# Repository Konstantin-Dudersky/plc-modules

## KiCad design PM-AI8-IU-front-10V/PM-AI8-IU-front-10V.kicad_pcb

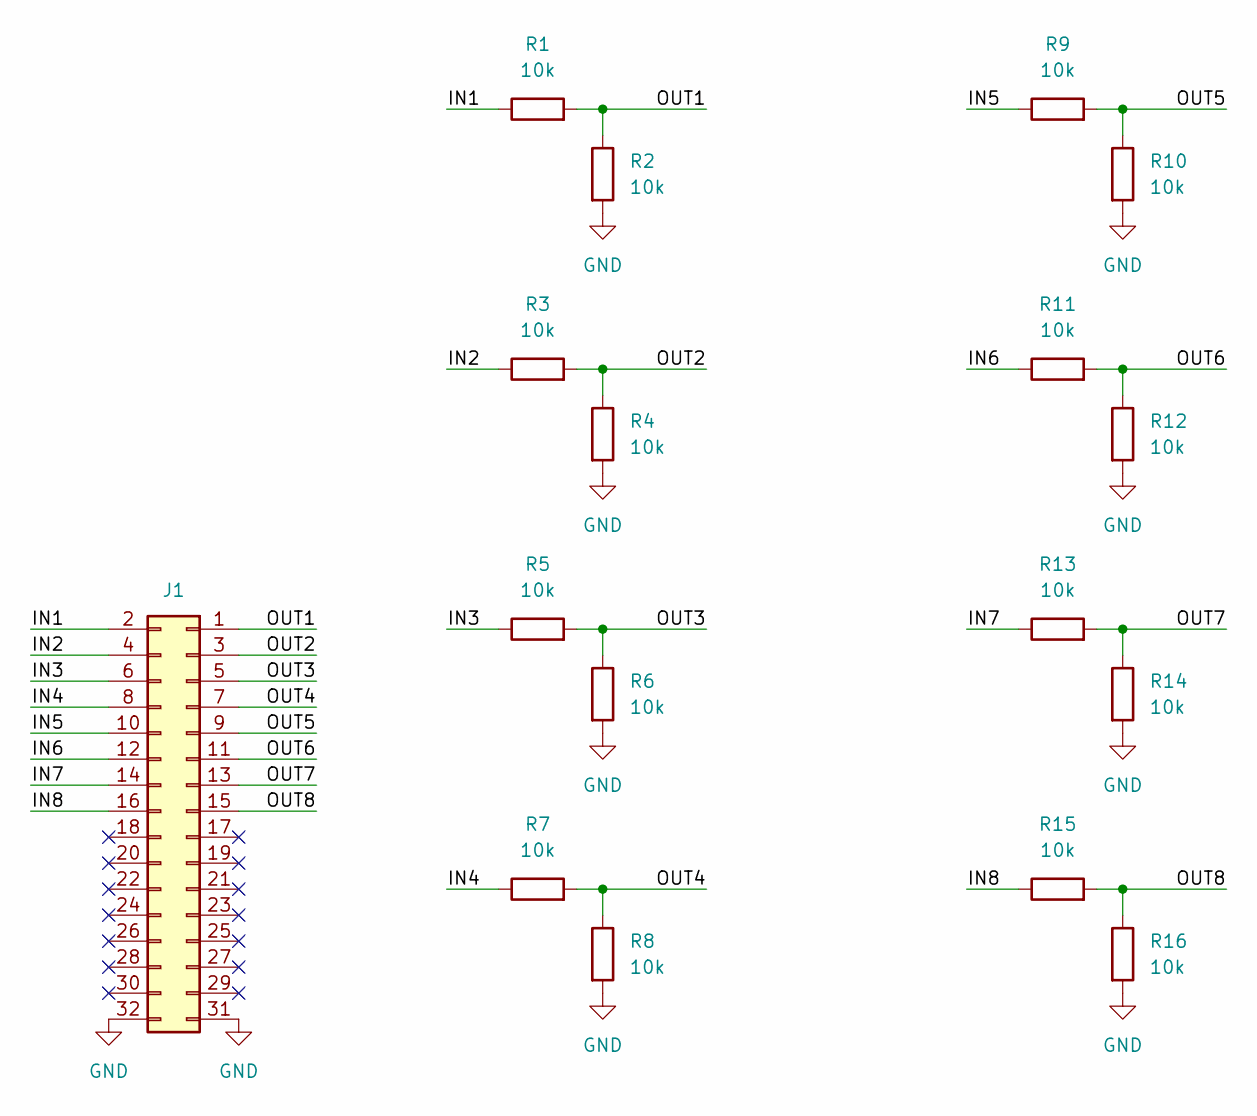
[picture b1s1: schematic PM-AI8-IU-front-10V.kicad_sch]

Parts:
J1: PinHeader P2.54 02x16 SMD Straight; PinHeader_2x16_P2.54mm_Vertical_SMD; part_ipn PinHeader P2.54 02x16 SMD Straight
R1, R2, R3, R4, R5, R6, R7, R8, R9, R10, R11, R12, R13, R14, R15, R16: 10k; R_1206_3216Metric_Pad1.30x1.75mm_HandSolder; part_ipn R_10k_1206_1%

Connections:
/IN1: J1.2, R1.1
/IN2: J1.4, R3.1
/IN3: J1.6, R5.1
/IN4: J1.8, R7.1
/IN5: J1.10, R9.1
/IN6: J1.12, R11.1
/IN7: J1.14, R13.1
/IN8: J1.16, R15.1
/OUT1: J1.1, R1.2, R2.1
/OUT2: J1.3, R3.2, R4.1
/OUT3: J1.5, R5.2, R6.1
/OUT4: J1.7, R7.2, R8.1
/OUT5: J1.9, R9.2, R10.1
/OUT6: J1.11, R11.2, R12.1
/OUT7: J1.13, R13.2, R14.1
/OUT8: J1.15, R15.2, R16.1
GND: J1.31, J1.32, R2.2, R4.2, R6.2, R8.2, R10.2, R12.2, R14.2, R16.2

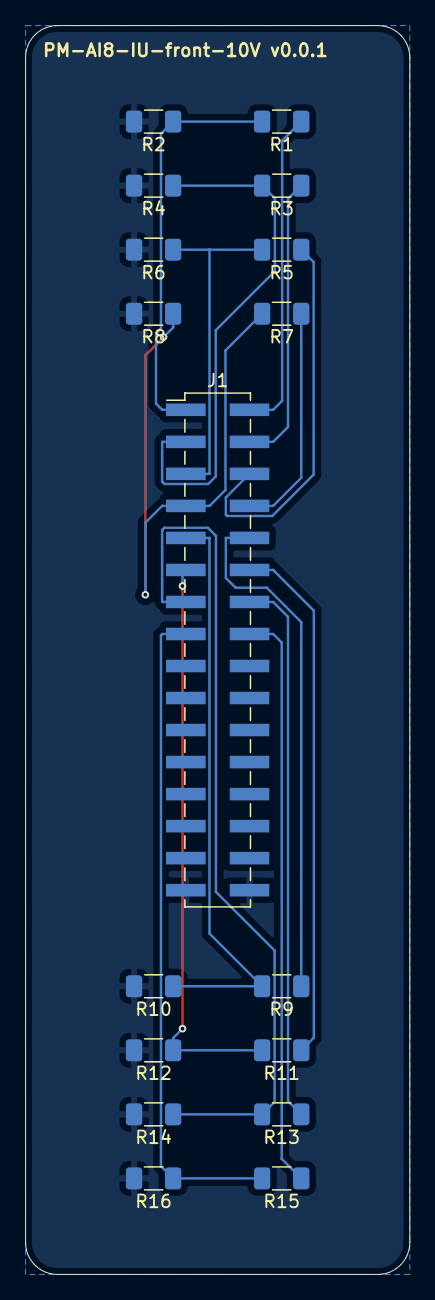
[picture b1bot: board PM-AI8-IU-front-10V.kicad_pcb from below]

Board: 2 copper layers, 30.5 x 99.1 mm, 17 parts (17 on the bottom side), 17 nets.

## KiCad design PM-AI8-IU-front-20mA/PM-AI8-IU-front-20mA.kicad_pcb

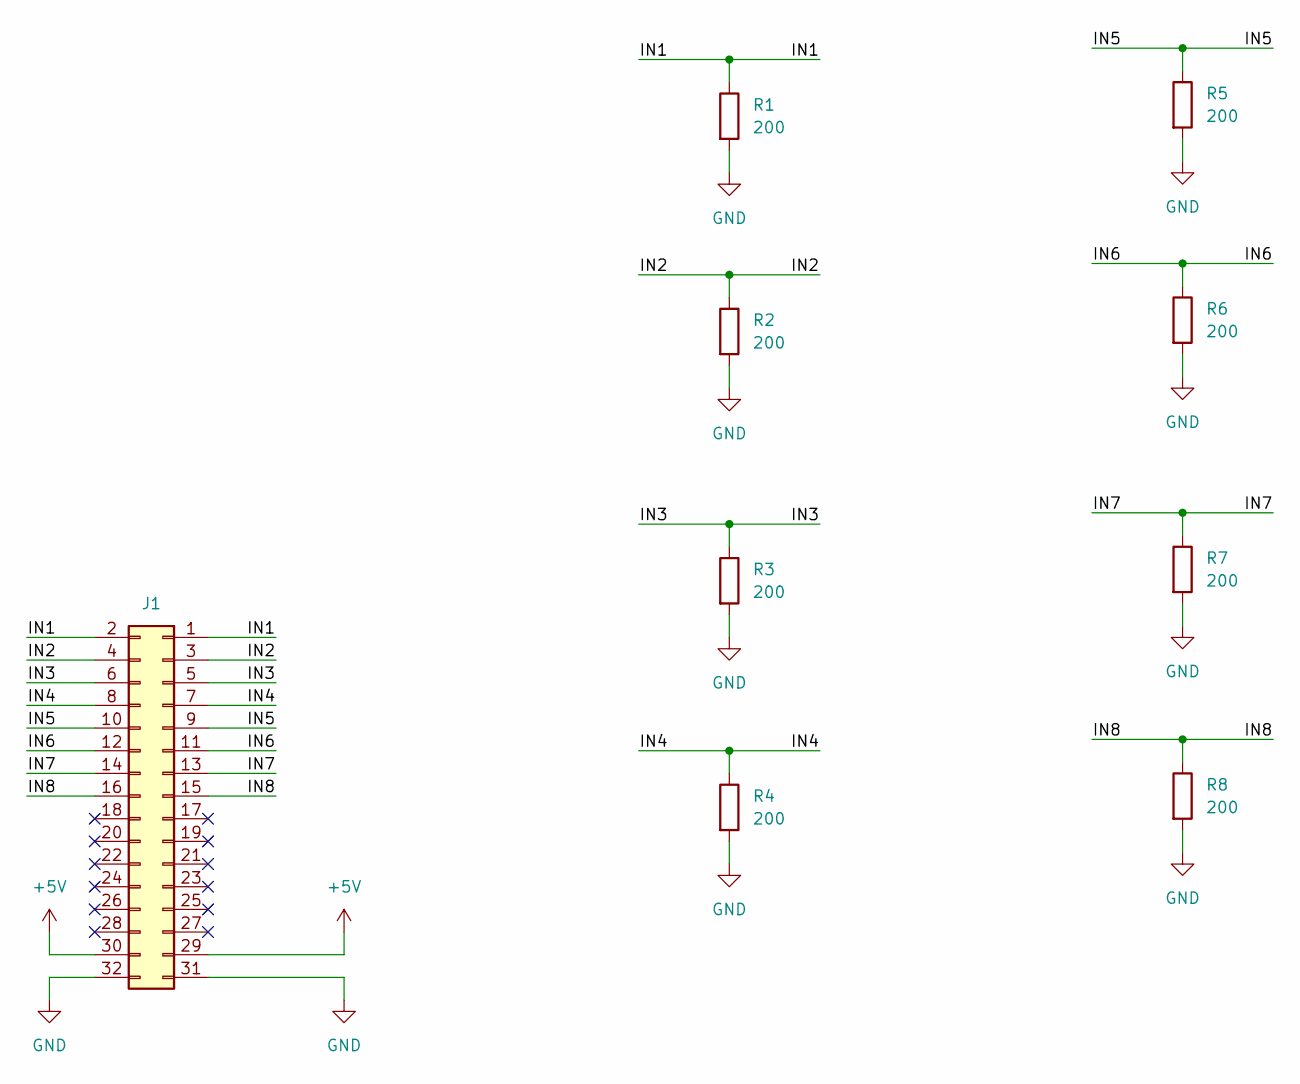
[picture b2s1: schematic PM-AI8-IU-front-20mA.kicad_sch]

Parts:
J1: PinHeader P2.54 02x16 SMD Straight; PinHeader_2x16_P2.54mm_Vertical_SMD; part_ipn PinHeader P2.54 02x16 SMD Straight
R1, R2, R3, R4, R5, R6, R7, R8: 200; R_1206_3216Metric_Pad1.30x1.75mm_HandSolder; part_ipn R_200_1206_0.1%

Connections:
+5V: J1.29, J1.30
/IN1: J1.1, J1.2, R1.1
/IN2: J1.3, J1.4, R2.1
/IN3: J1.5, J1.6, R3.1
/IN4: J1.7, J1.8, R4.1
/IN5: J1.9, J1.10, R5.1
/IN6: J1.11, J1.12, R6.1
/IN7: J1.13, J1.14, R7.1
/IN8: J1.15, J1.16, R8.1
GND: J1.31, J1.32, R1.2, R2.2, R3.2, R4.2, R5.2, R6.2, R7.2, R8.2

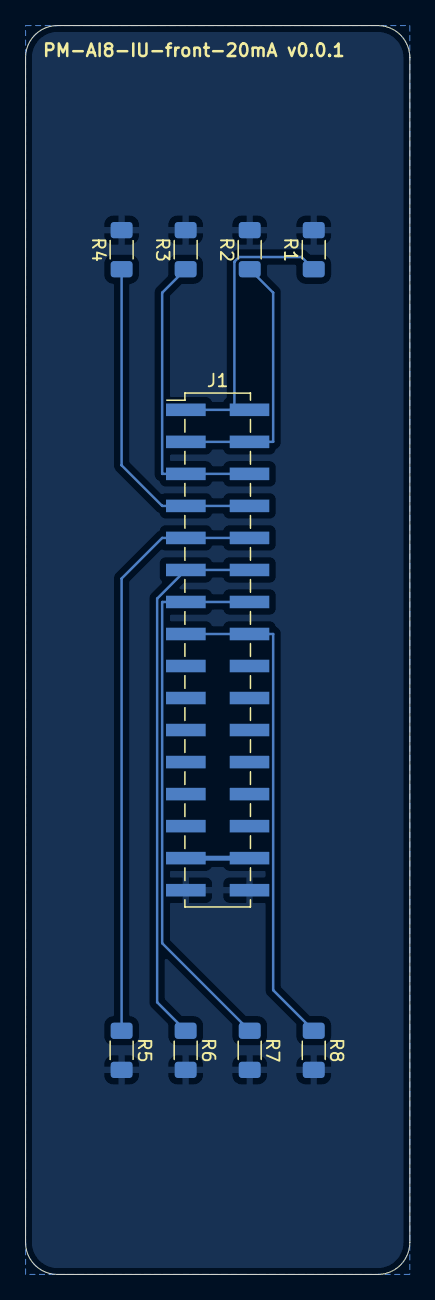
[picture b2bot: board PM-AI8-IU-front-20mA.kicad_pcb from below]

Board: 2 copper layers, 30.5 x 99.1 mm, 9 parts (9 on the bottom side), 10 nets.

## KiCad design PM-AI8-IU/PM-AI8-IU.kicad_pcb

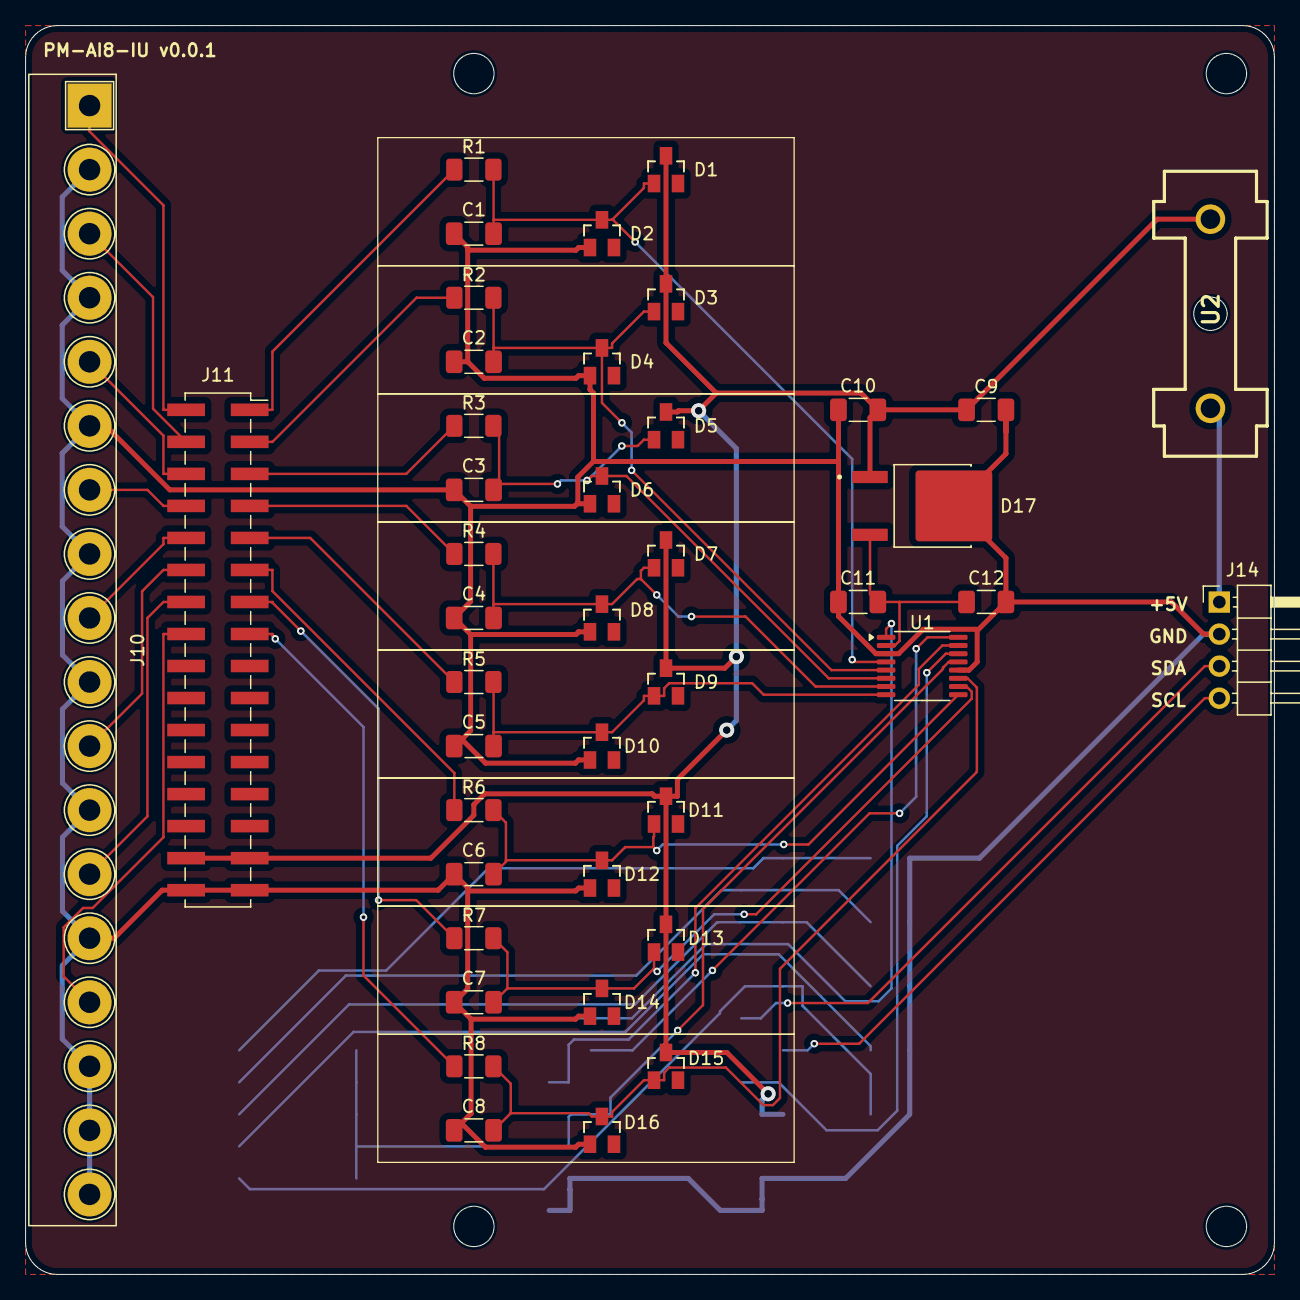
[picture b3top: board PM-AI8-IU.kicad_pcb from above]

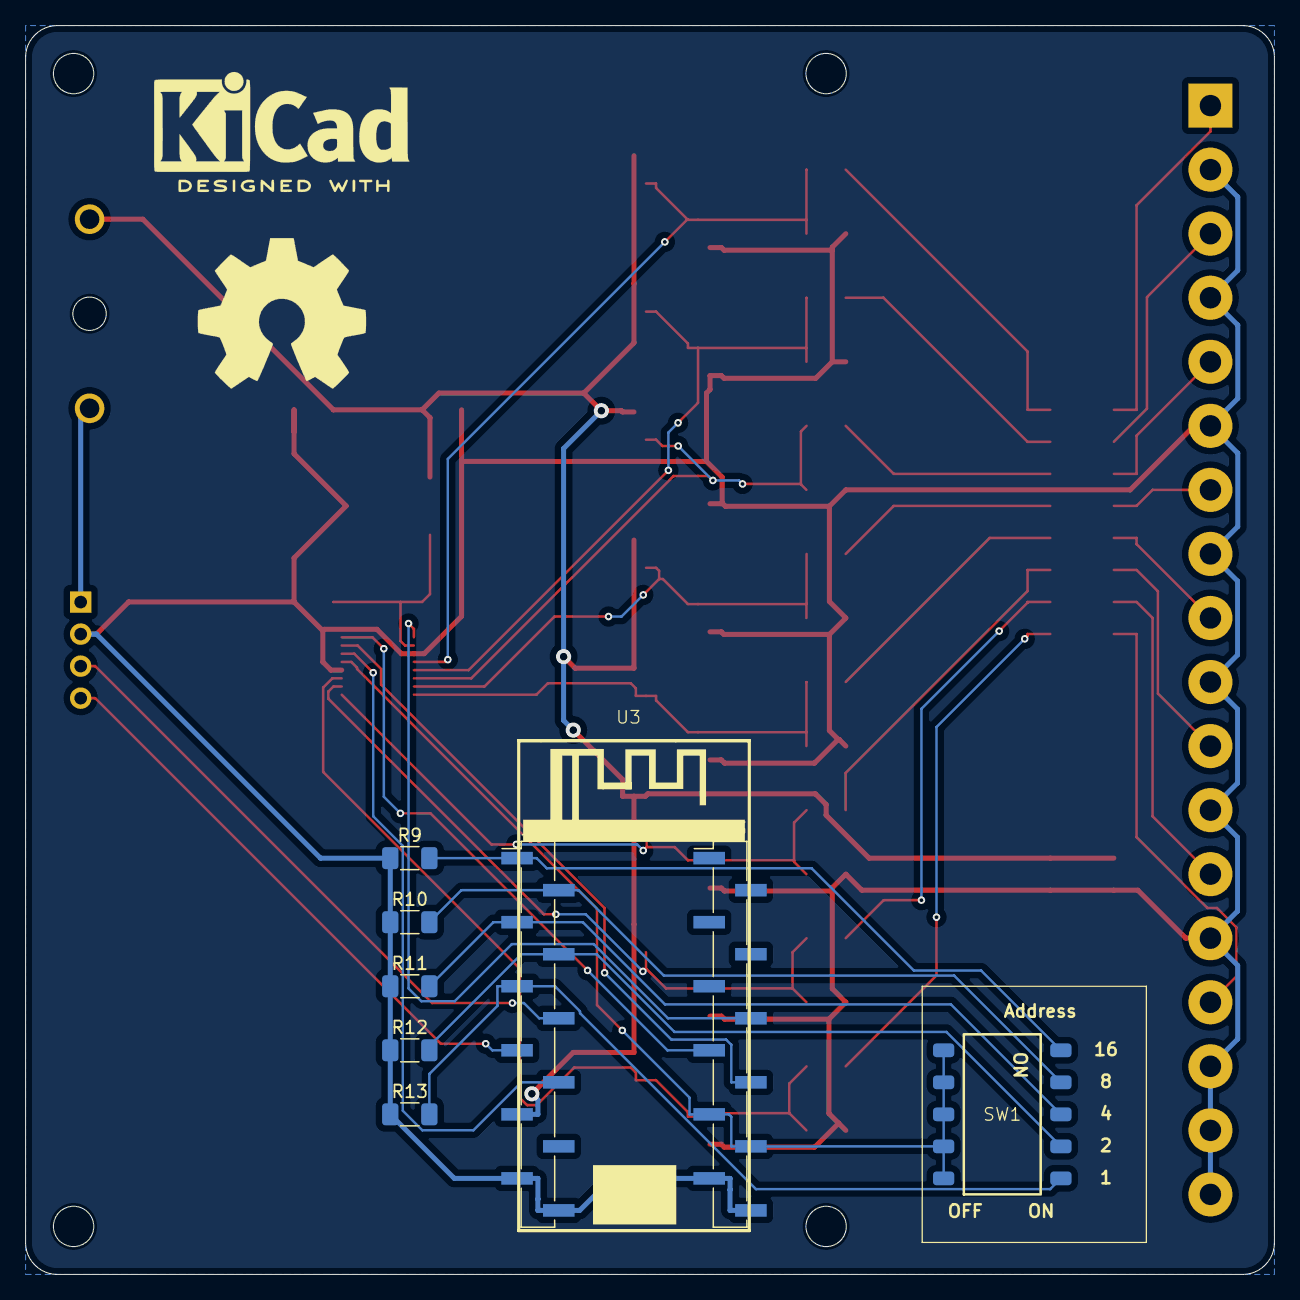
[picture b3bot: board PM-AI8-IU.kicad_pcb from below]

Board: 2 copper layers, 99.1 x 99.1 mm, 57 parts (11 on the bottom side), 40 nets.

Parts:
C1, C2, C3, C4, C5, C6, C7, C8: 33nF; C_1206_3216Metric_Pad1.33x1.80mm_HandSolder
C9, C11: 100nF 1206; C_1206_3216Metric_Pad1.33x1.80mm_HandSolder
C10, C12: 1uF 1206; C_1206_3216Metric_Pad1.33x1.80mm_HandSolder
D1, D2, D3, D4, D5, D6, D7, D8, D9, D10, D11, D12, D13, D14, D15, D16: BAT54; BAT54_SOT23
D17: LP2950CDT-5.0RKG
H1, H2, H3, H4: MountingHole; MountingHole_3.2mm_M3
J10: 2EDGR-5.08-18P; Degson_2EDGR-5.08-18P
J11: FemaleHeader P2.54 02x16 SMD Straight; PinSocket_2x16_P2.54mm_Vertical_SMD
J12, J13: PinHeader P2.54 01x12 SMD Straight; PinHeader_1x12_P2.54mm_Vertical_SMD_Pin1Left
J14: Conn_01x04_Pin; PinHeader_1x04_P2.54mm_Horizontal
R1, R2, R3, R4, R5, R6, R7, R8: 100; R_1206_3216Metric_Pad1.30x1.75mm_HandSolder
R9, R10, R11, R12, R13: 10k; R_1206_3216Metric_Pad1.30x1.75mm_HandSolder
SW1: DSIC05LS-P
U1: ADC128S102CIMT; TSSOP-16_4.4x5mm_P0.65mm
U2: 64900001039; Fuseholder
U3: Weact ESP32-C3FH4
logo_kicad: KiCad-Logo2_8mm_SilkScreen
logo_oshw: OSHW-Symbol_13.4x12mm_SilkScreen

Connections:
+3.3V: J13.9, J13.10, SW1.6, SW1.7, SW1.8, SW1.9, SW1.10, U1.13 (DVCC)
+5V: C9.1, C10.1, D1.3, D3.3, D5.3, D7.3, D9.3, D11.3, D13.3, D15.3, D17.1 (In), J11.29, J11.30, J12.9, U2.1
/AIN0: C1.1, D1.1, D2.3, R1.2, U1.4 (IN0)
/AIN1: C2.1, D3.1, D4.3, R2.2, U1.5 (IN1)
/AIN2: C3.1, D5.1, D6.3, R3.2, U1.6 (IN2)
/AIN3: C4.1, D7.1, D8.3, R4.2, U1.7 (IN3)
/AIN4: C5.1, D9.1, D10.3, R5.2, U1.8 (IN4)
/AIN5: C6.1, D11.1, D12.3, R6.2, U1.9 (IN5)
/AIN6: C7.1, D13.1, D14.3, R7.2, U1.10 (IN6)
/AIN7: C8.1, D15.1, D16.3, R8.2, U1.11 (IN7)
/AVCC: C11.1, C12.1, D17.3 (Out), U1.2 (AVCC)
/CLK: J13.7, U1.16 (SCLK)
/CS: J13.6, U1.1 (~CS)
/MISO: J13.8, U1.15 (DOUT)
/MOSI: J12.8, U1.14 (DIN)
/SCL: J12.7, J14.4
/SDA: J12.6, J14.3
GND: C1.2, C2.2, C3.2, C4.2, C5.2, C6.2, C7.2, C8.2, C9.2, C10.2, C11.2, C12.2, D2.1, D4.1, D6.1, D8.1, D10.1, D12.1, D14.1, D16.1, D17.4 (Gnd), J10.2, J10.4, J10.6, J10.8, J10.10, J10.12, J10.14, J10.16, J10.17, J10.18, J11.31, J11.32, J12.11, J12.12, J13.11, J13.12, J14.2, R9.1, R10.1, R11.1, R12.1, R13.1, U1.3 (AGND), U1.12 (DGND)
unnamed: J10.1, J11.2
unnamed: J10.3, J11.4
unnamed: J10.5, J11.6
unnamed: J10.7, J11.8
unnamed: J10.9, J11.10
unnamed: J10.11, J11.12
unnamed: J10.13, J11.14
unnamed: J10.15, J11.16
unnamed: J11.1, R1.1
unnamed: J11.3, R2.1
unnamed: J11.5, R3.1
unnamed: J11.7, R4.1
unnamed: J11.9, R5.1
unnamed: J11.11, R6.1
unnamed: J11.13, R7.1
unnamed: J11.15, R8.1
unnamed: J12.1, R9.2, SW1.5
unnamed: J12.2, R10.2, SW1.4
unnamed: J12.3, R11.2, SW1.3
unnamed: J12.4, R12.2, SW1.2
unnamed: J12.5, R13.2, SW1.1
unnamed: J14.1, U2.2

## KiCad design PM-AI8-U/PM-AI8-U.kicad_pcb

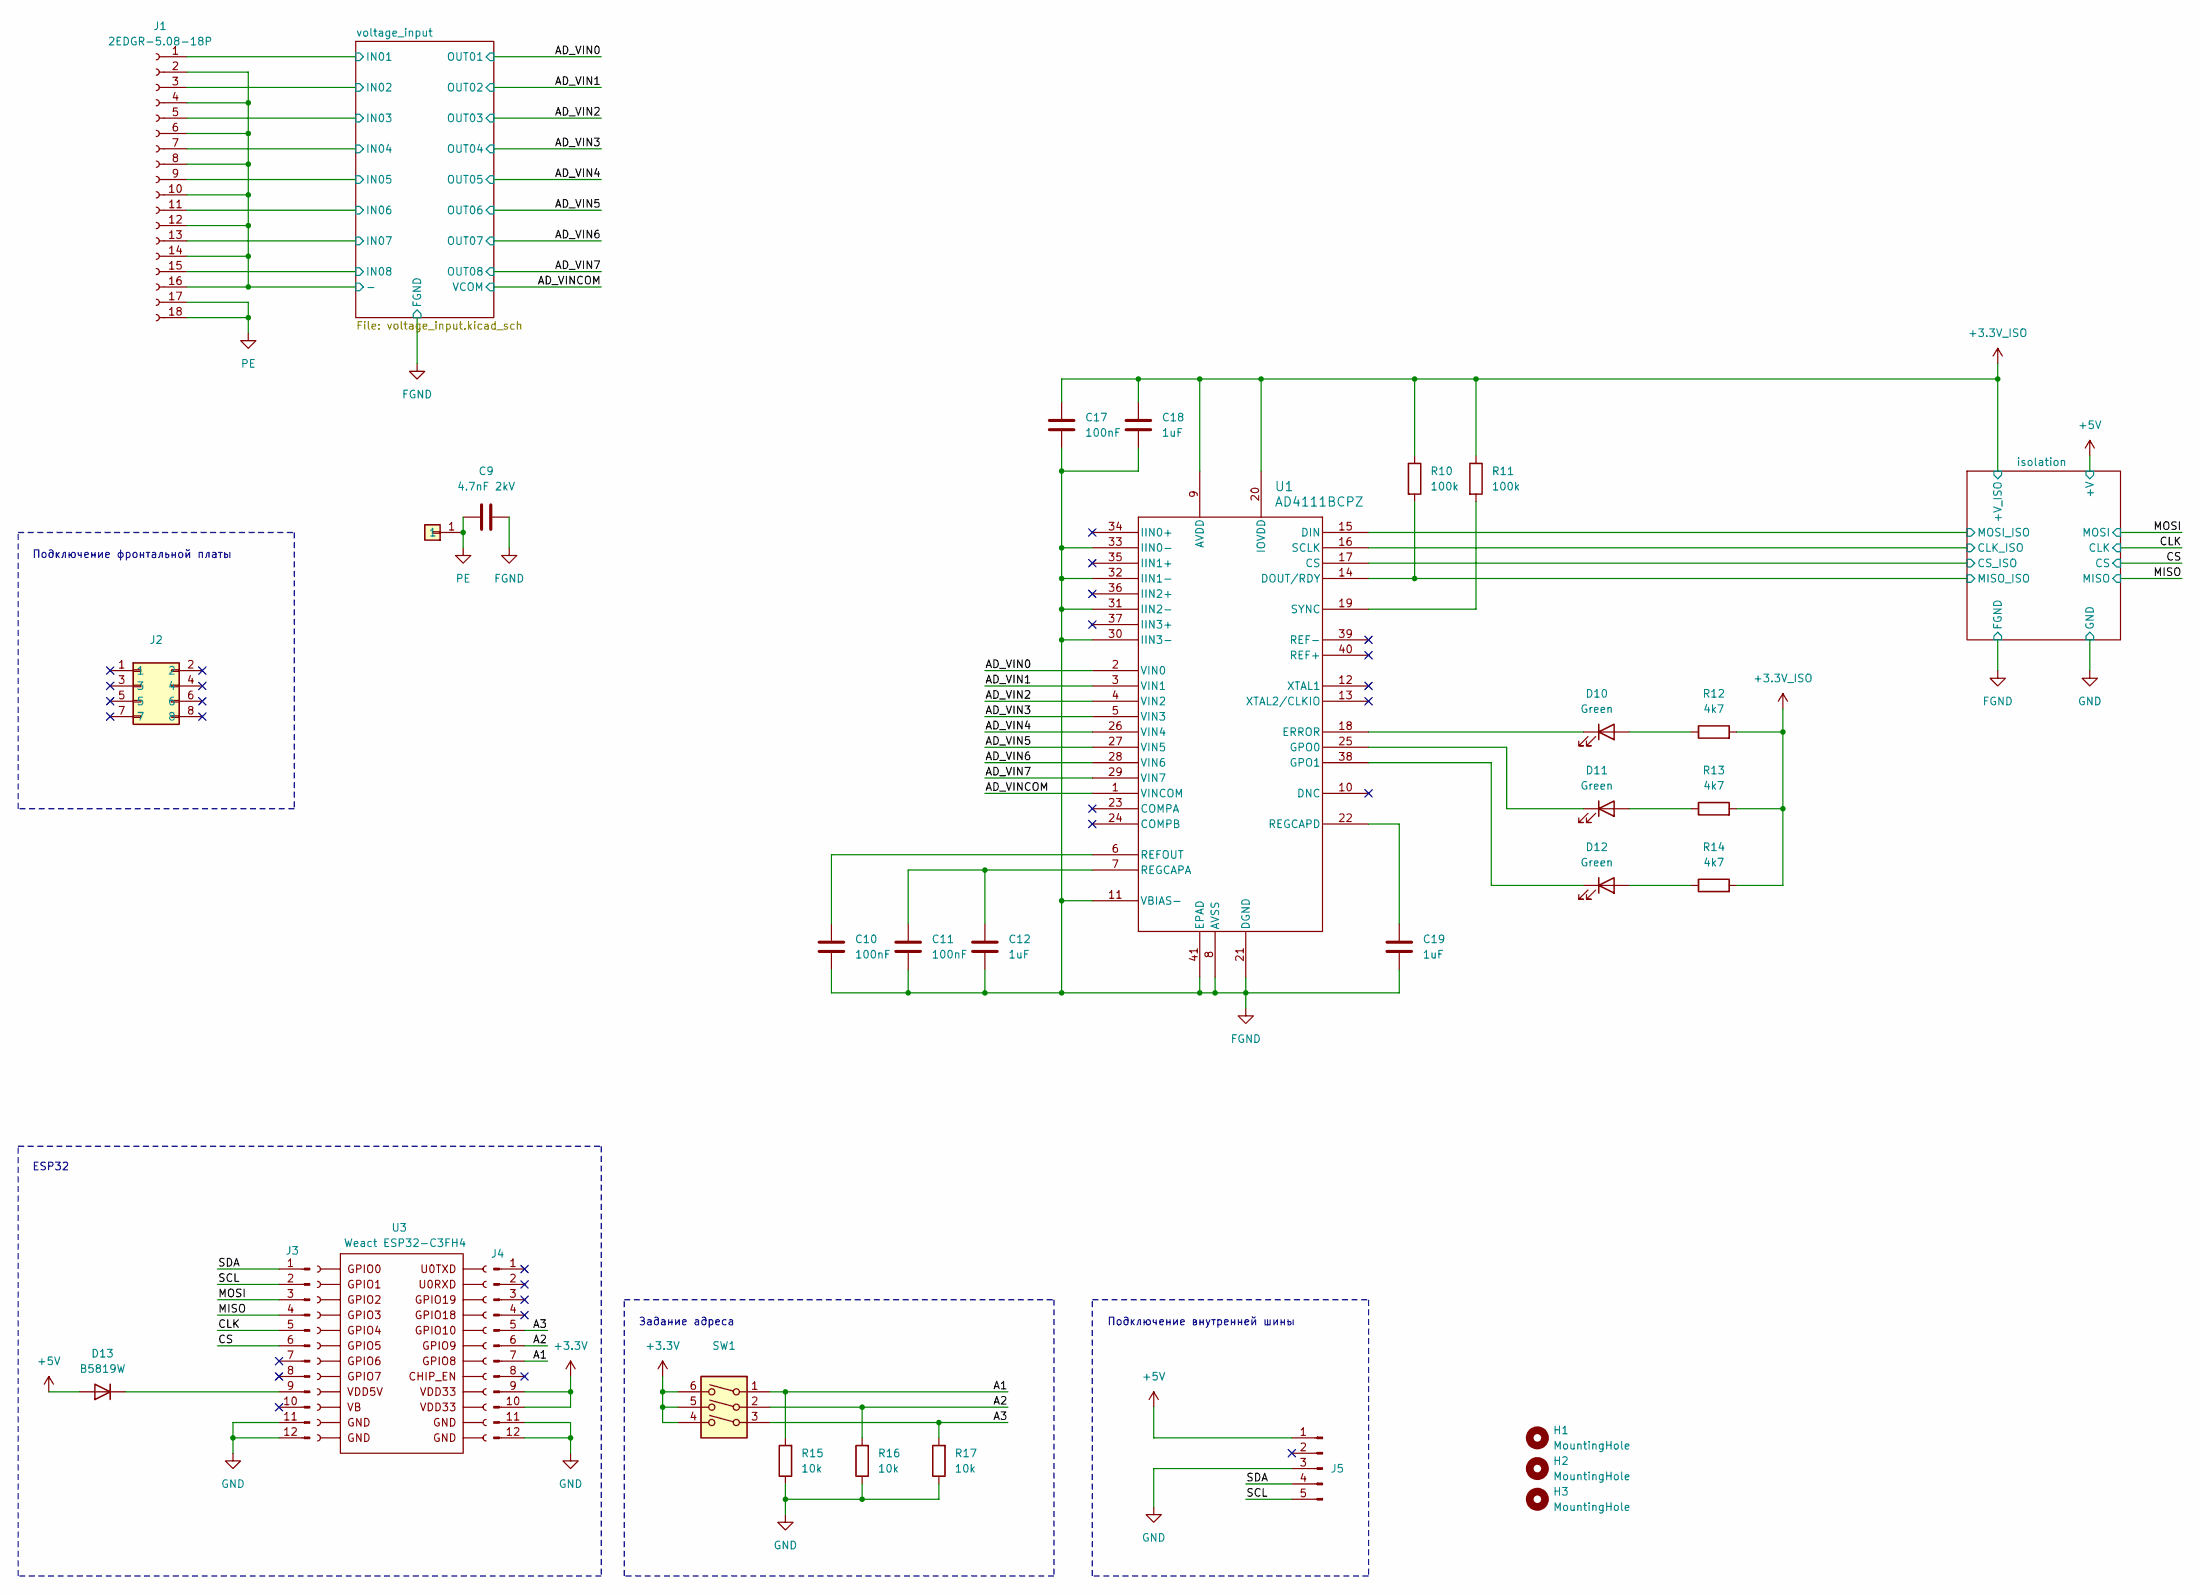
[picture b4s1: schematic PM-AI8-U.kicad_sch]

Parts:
C9: 4.7nF 2kV; C_1812_4532Metric_Pad1.57x3.40mm_HandSolder; part_ipn C_4.7nF_2kV_1812
C10, C11, C17: 100nF; C_1206_3216Metric_Pad1.33x1.80mm_HandSolder; part_ipn C_100nF_50V_1206
C12, C18, C19: 1uF; C_1206_3216Metric_Pad1.33x1.80mm_HandSolder; part_ipn C_1uF_50V_1206
D9: PE
D10, D11, D12: Green; LED_1206_3216Metric_Pad1.42x1.75mm_HandSolder; part_ipn LED_green_1206
D13: B5819W; D_SOD-123; part_ipn B5819W
H1, H2, H3: MountingHole; MountingHole_3.2mm_M3
J1: 2EDGR-5.08-18P; Degson_2EDGR-5.08-18P; part_ipn 2EDGR-5.08-18P
J2: PM-front-02x04
J3, J4: PinHeader P2.54 01x12 THT Straight; PinHeader_1x12_P2.54mm_Vertical; part_ipn PinHeader_01x12_P2.54_THT_straight
J5: PinHeader_01x05_P2.54_THT_angle; PinHeader_1x05_P2.54mm_Horizontal; part_ipn PinHeader_01x05_P2.54_THT_angle
R10, R11: 100k; R_1206_3216Metric_Pad1.30x1.75mm_HandSolder; part_ipn R_100k_1206_1%
R12, R13, R14: 4k7; R_1206_3216Metric_Pad1.30x1.75mm_HandSolder; part_ipn R_4k7_1206_1%
R15, R16, R17: 10k; R_1206_3216Metric_Pad1.30x1.75mm_HandSolder; part_ipn R_10k_1206_1%
SW1: DIP_SW-3P-P2.54-THT-Top; SW_DIP_SPSTx03_Slide_9.78x9.8mm_W7.62mm_P2.54mm; part_ipn DIP_SW-3P-P2.54-THT-Top
U1: AD4111BCPZ; AD4111BCPZ_ADI; part_ipn AD4111BCPZ
U3: Weact ESP32-C3FH4; part_ipn Weact ESP32-C3FH4

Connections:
+3.3V: J4.9, J4.10, SW1.4, SW1.5, SW1.6
+3.3V_ISO: C17.1, C18.1, R10.1, R11.1, R12.2, R13.2, R14.2, U1.9 (AVDD), U1.20 (IOVDD); also elsewhere on the board
+5V: D13.2 (A), J5.1; also elsewhere on the board
/A1: J4.7, R15.2, SW1.1
/A2: J4.6, R16.2, SW1.2
/A3: J4.5, R17.2, SW1.3
/AD_VIN0: U1.2 (VIN0); also elsewhere on the board
/AD_VIN1: U1.3 (VIN1); also elsewhere on the board
/AD_VIN2: U1.4 (VIN2); also elsewhere on the board
/AD_VIN3: U1.5 (VIN3); also elsewhere on the board
/AD_VIN4: U1.26 (VIN4); also elsewhere on the board
/AD_VIN5: U1.27 (VIN5); also elsewhere on the board
/AD_VIN6: U1.28 (VIN6); also elsewhere on the board
/AD_VIN7: U1.29 (VIN7); also elsewhere on the board
/CLK: J3.5; also elsewhere on the board
/CS: J3.6; also elsewhere on the board
/MISO: J3.4; also elsewhere on the board
/MOSI: J3.3; also elsewhere on the board
/SCL: J3.2, J5.5
/SDA: J3.1, J5.4
/isolation/CLK_ISO: U1.16 (SCLK); also elsewhere on the board
/isolation/CS_ISO: U1.17 (CS); also elsewhere on the board
/isolation/MISO_ISO: R10.2, U1.14 (DOUT/RDY); also elsewhere on the board
/isolation/MOSI_ISO: U1.15 (DIN); also elsewhere on the board
/voltage_input/IN01: J1.1; also elsewhere on the board
/voltage_input/IN02: J1.3; also elsewhere on the board
/voltage_input/IN03: J1.5; also elsewhere on the board
/voltage_input/IN04: J1.7; also elsewhere on the board
/voltage_input/IN05: J1.9; also elsewhere on the board
/voltage_input/IN06: J1.11; also elsewhere on the board
/voltage_input/IN07: J1.13; also elsewhere on the board
/voltage_input/IN08: J1.15; also elsewhere on the board
FGND: C9.2, C10.2, C11.2, C12.2, C17.2, C18.2, C19.2, J1.2, J1.4, J1.6, J1.8, J1.10, J1.12, J1.14, J1.16, U1.1 (VINCOM), U1.8 (AVSS), U1.11 (VBIAS-), U1.21 (DGND), U1.30 (IIN3-), U1.31 (IIN2-), U1.32 (IIN1-), U1.33 (IIN0-), U1.41 (EPAD); also elsewhere on the board
GND: J3.11, J3.12, J4.11, J4.12, J5.3, R15.1, R16.1, R17.1; also elsewhere on the board
unnamed: D10.2 (A), R12.1
unnamed: D10.1 (K), U1.18 (ERROR)
unnamed: D11.2 (A), R13.1
unnamed: D11.1 (K), U1.25 (GPO0)
unnamed: D12.2 (A), R14.1
unnamed: D12.1 (K), U1.38 (GPO1)
unnamed: D13.1 (K), J3.9
unnamed: C10.1, U1.6 (REFOUT)
unnamed: C11.1, C12.1, U1.7 (REGCAPA)
unnamed: C19.1, U1.22 (REGCAPD)
unnamed: R11.2, U1.19 (SYNC)
PE: C9.1, D9.1, J1.17, J1.18

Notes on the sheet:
ESP32
Подключение фронтальной платы
Задание адреса
Подключение внутренней шины

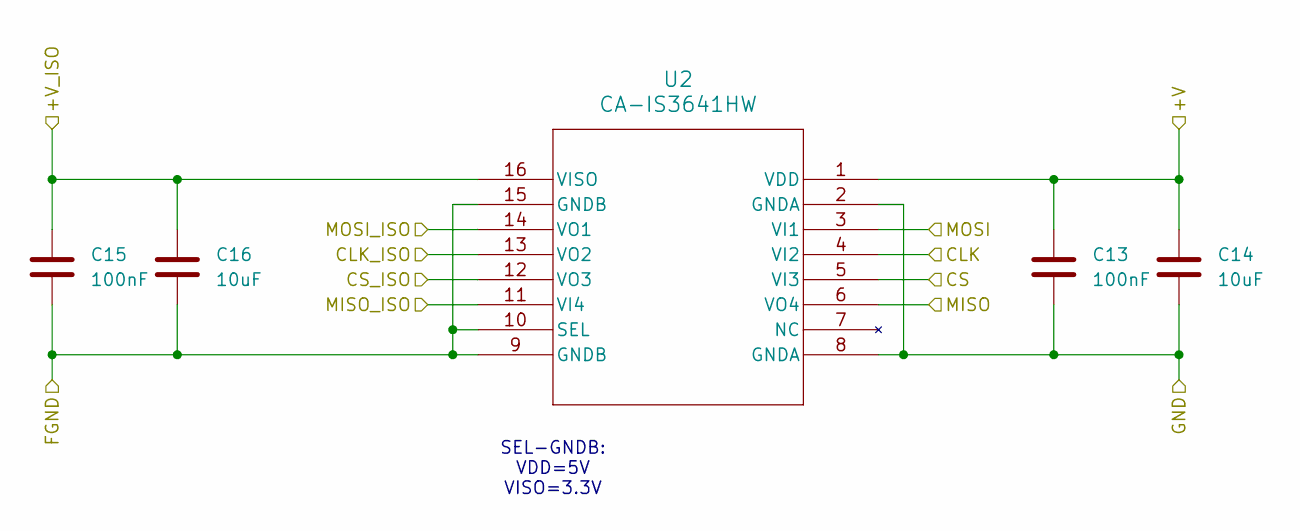
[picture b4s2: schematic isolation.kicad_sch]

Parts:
C13, C15: 100nF; C_1206_3216Metric_Pad1.33x1.80mm_HandSolder; part_ipn C_100nF_50V_1206
C14, C16: 10uF; C_1210_3225Metric_Pad1.33x2.70mm_HandSolder; part_ipn C_10uF_50V_1210
U2: CA-IS3641HW; SOIC16-WBW_CLG-M; part_ipn CA-IS3641HW

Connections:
+3.3V_ISO: C15.1, C16.1, U2.16 (VISO); also elsewhere on the board
+5V: C13.1, C14.1, U2.1 (VDD); also elsewhere on the board
/CLK: U2.4 (VI2); also elsewhere on the board
/CS: U2.5 (VI3); also elsewhere on the board
/MISO: U2.6 (VO4); also elsewhere on the board
/MOSI: U2.3 (VI1); also elsewhere on the board
/isolation/CLK_ISO: U2.13 (VO2); also elsewhere on the board
/isolation/CS_ISO: U2.12 (VO3); also elsewhere on the board
/isolation/MISO_ISO: U2.11 (VI4); also elsewhere on the board
/isolation/MOSI_ISO: U2.14 (VO1); also elsewhere on the board
FGND: C15.2, C16.2, U2.9 (GNDB), U2.10 (SEL), U2.15 (GNDB); also elsewhere on the board
GND: C13.2, C14.2, U2.2 (GNDA), U2.8 (GNDA); also elsewhere on the board

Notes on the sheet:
SEL-GNDB: VDD=5V VISO=3.3V

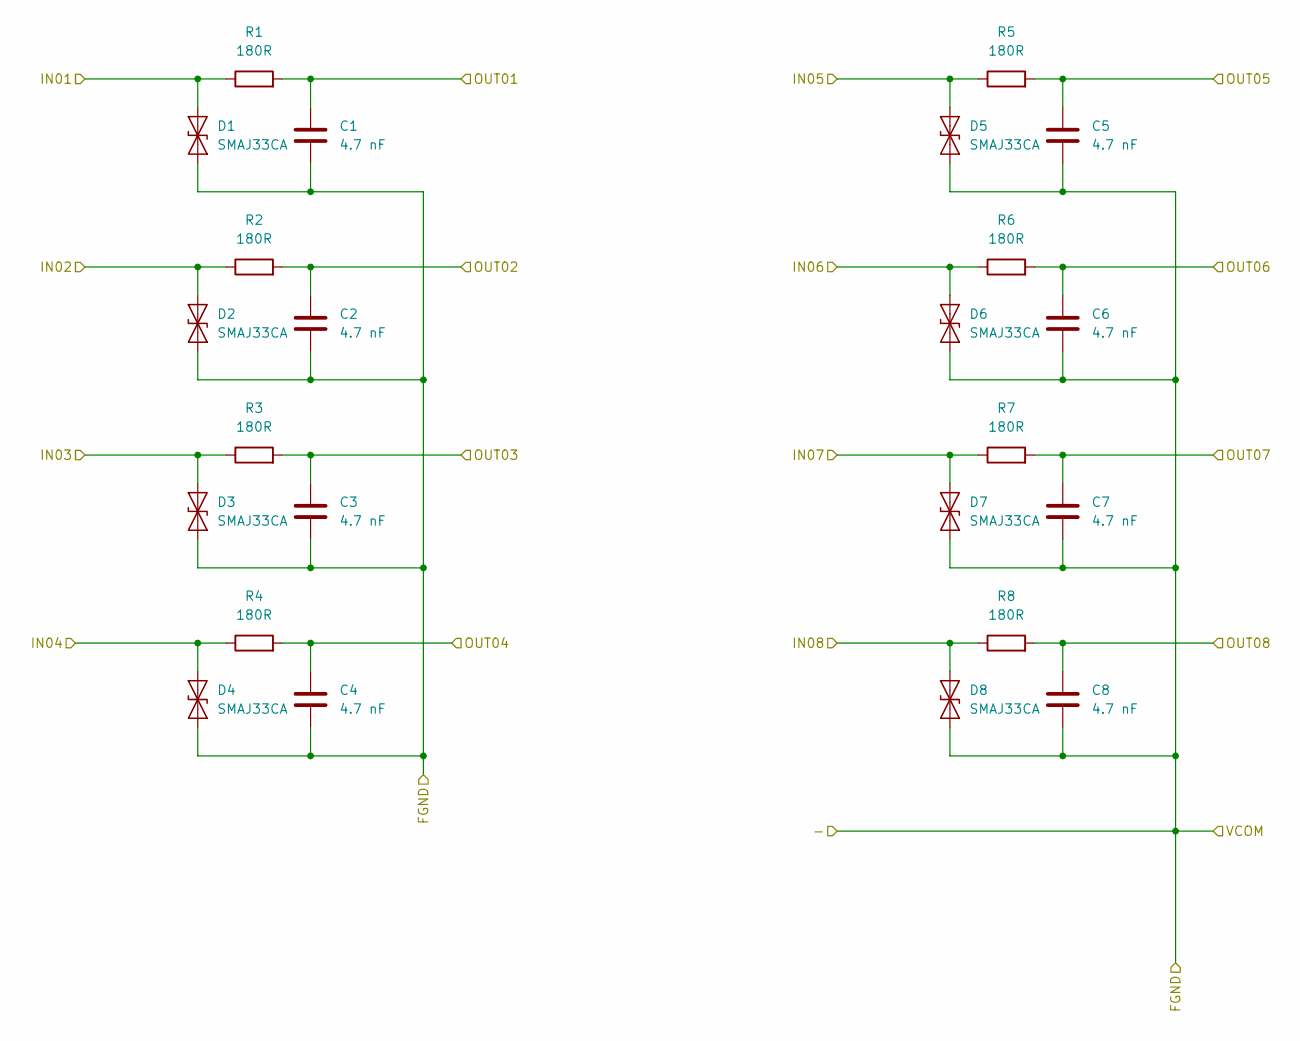
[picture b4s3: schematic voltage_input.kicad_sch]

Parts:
C1, C2, C3, C4, C5, C6, C7, C8: 4.7 nF; C_1206_3216Metric_Pad1.33x1.80mm_HandSolder; part_ipn C_4.7nF_50V_1206
D1, D2, D3, D4, D5, D6, D7, D8: SMAJ33CA; SMASeries_LTF-M; part_ipn SMAJ33CA
R1, R2, R3, R4, R5, R6, R7, R8: 180R; R_1206_3216Metric_Pad1.30x1.75mm_HandSolder; part_ipn R_180R_1206_1%

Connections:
/AD_VIN0: C1.1, R1.2; also elsewhere on the board
/AD_VIN1: C2.1, R2.2; also elsewhere on the board
/AD_VIN2: C3.1, R3.2; also elsewhere on the board
/AD_VIN3: C4.1, R4.2; also elsewhere on the board
/AD_VIN4: C5.1, R5.2; also elsewhere on the board
/AD_VIN5: C6.1, R6.2; also elsewhere on the board
/AD_VIN6: C7.1, R7.2; also elsewhere on the board
/AD_VIN7: C8.1, R8.2; also elsewhere on the board
/voltage_input/IN01: D1.2 (A2), R1.1; also elsewhere on the board
/voltage_input/IN02: D2.2 (A2), R2.1; also elsewhere on the board
/voltage_input/IN03: D3.2 (A2), R3.1; also elsewhere on the board
/voltage_input/IN04: D4.2 (A2), R4.1; also elsewhere on the board
/voltage_input/IN05: D5.2 (A2), R5.1; also elsewhere on the board
/voltage_input/IN06: D6.2 (A2), R6.1; also elsewhere on the board
/voltage_input/IN07: D7.2 (A2), R7.1; also elsewhere on the board
/voltage_input/IN08: D8.2 (A2), R8.1; also elsewhere on the board
FGND: C1.2, C2.2, C3.2, C4.2, C5.2, C6.2, C7.2, C8.2, D1.1 (A1), D2.1 (A1), D3.1 (A1), D4.1 (A1), D5.1 (A1), D6.1 (A1), D7.1 (A1), D8.1 (A1); also elsewhere on the board

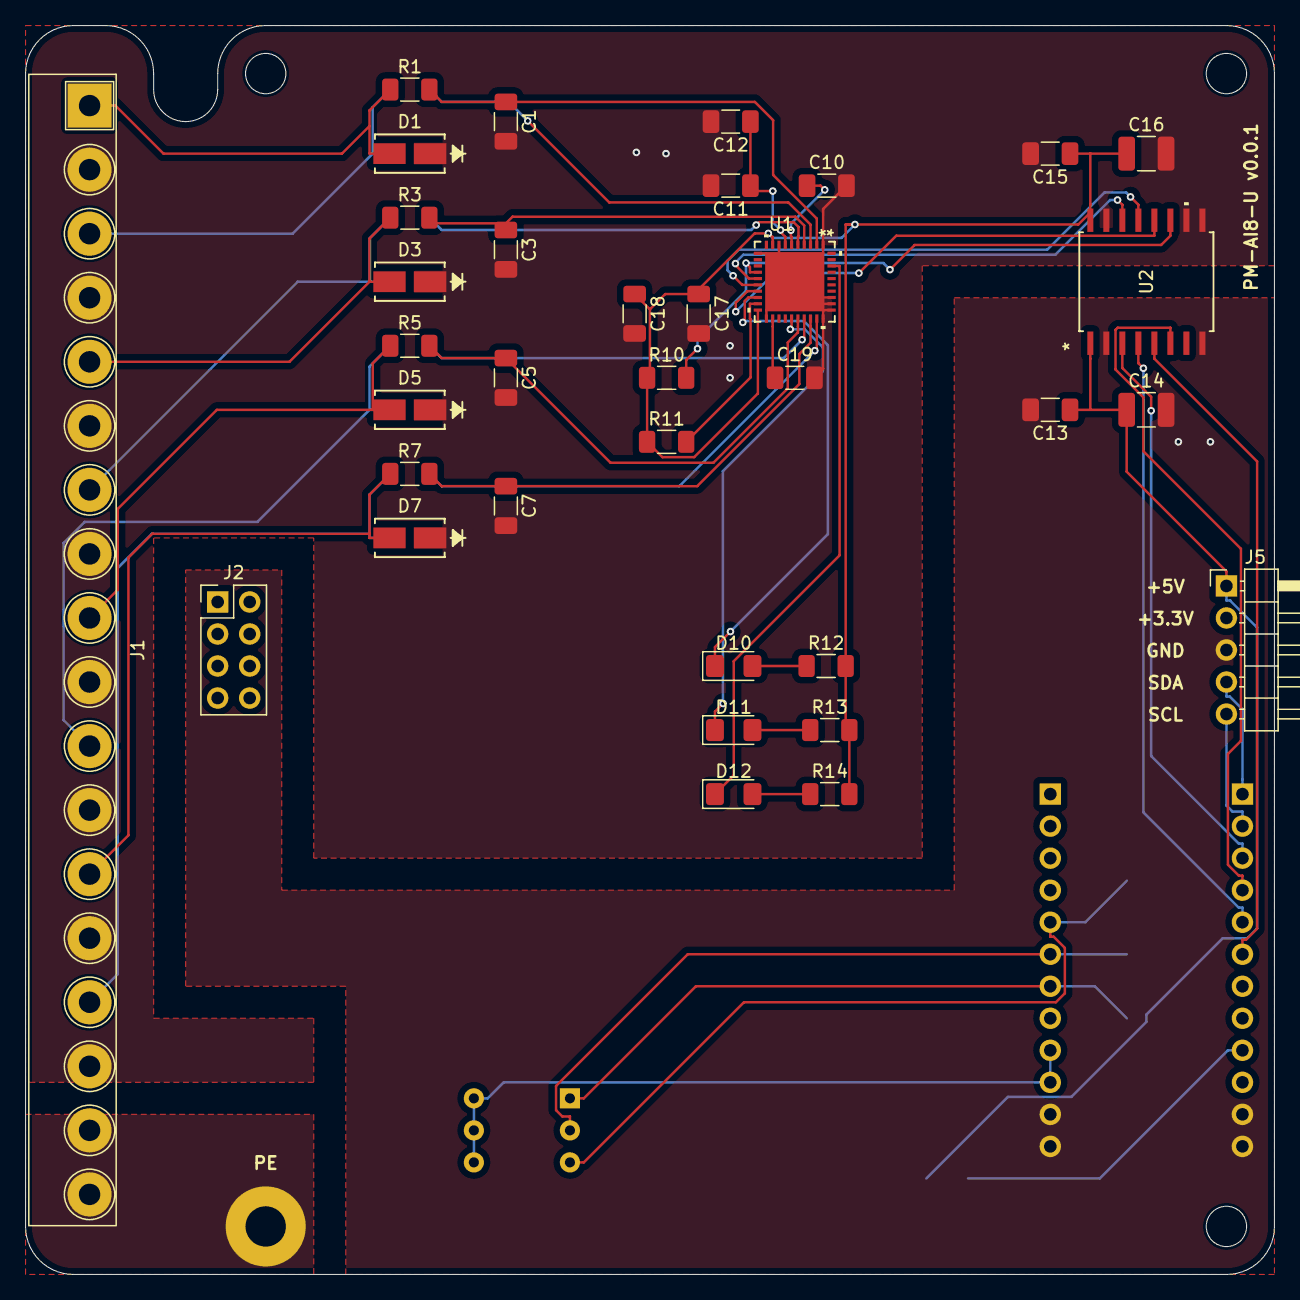
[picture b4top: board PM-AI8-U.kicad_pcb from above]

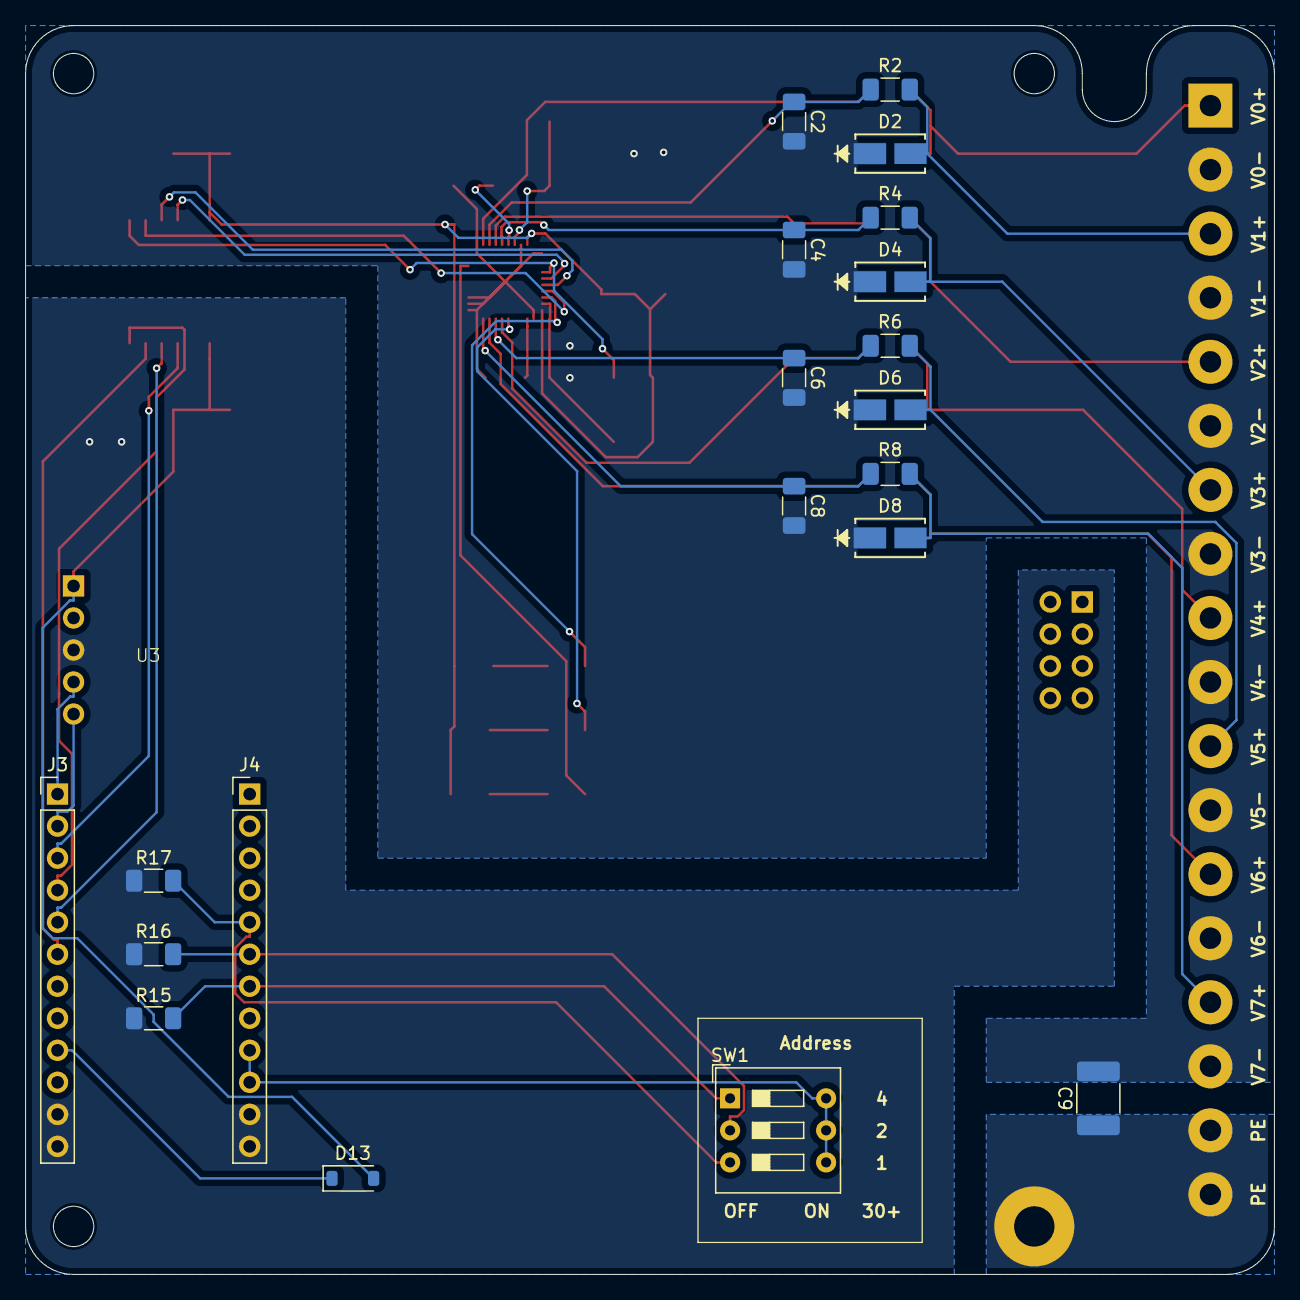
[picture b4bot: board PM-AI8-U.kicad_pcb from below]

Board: 2 copper layers, 99.1 x 99.1 mm, 60 parts (21 on the bottom side), 46 nets.
